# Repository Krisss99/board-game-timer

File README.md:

# board-game-timer
Timer measures players' time taken in their turn.

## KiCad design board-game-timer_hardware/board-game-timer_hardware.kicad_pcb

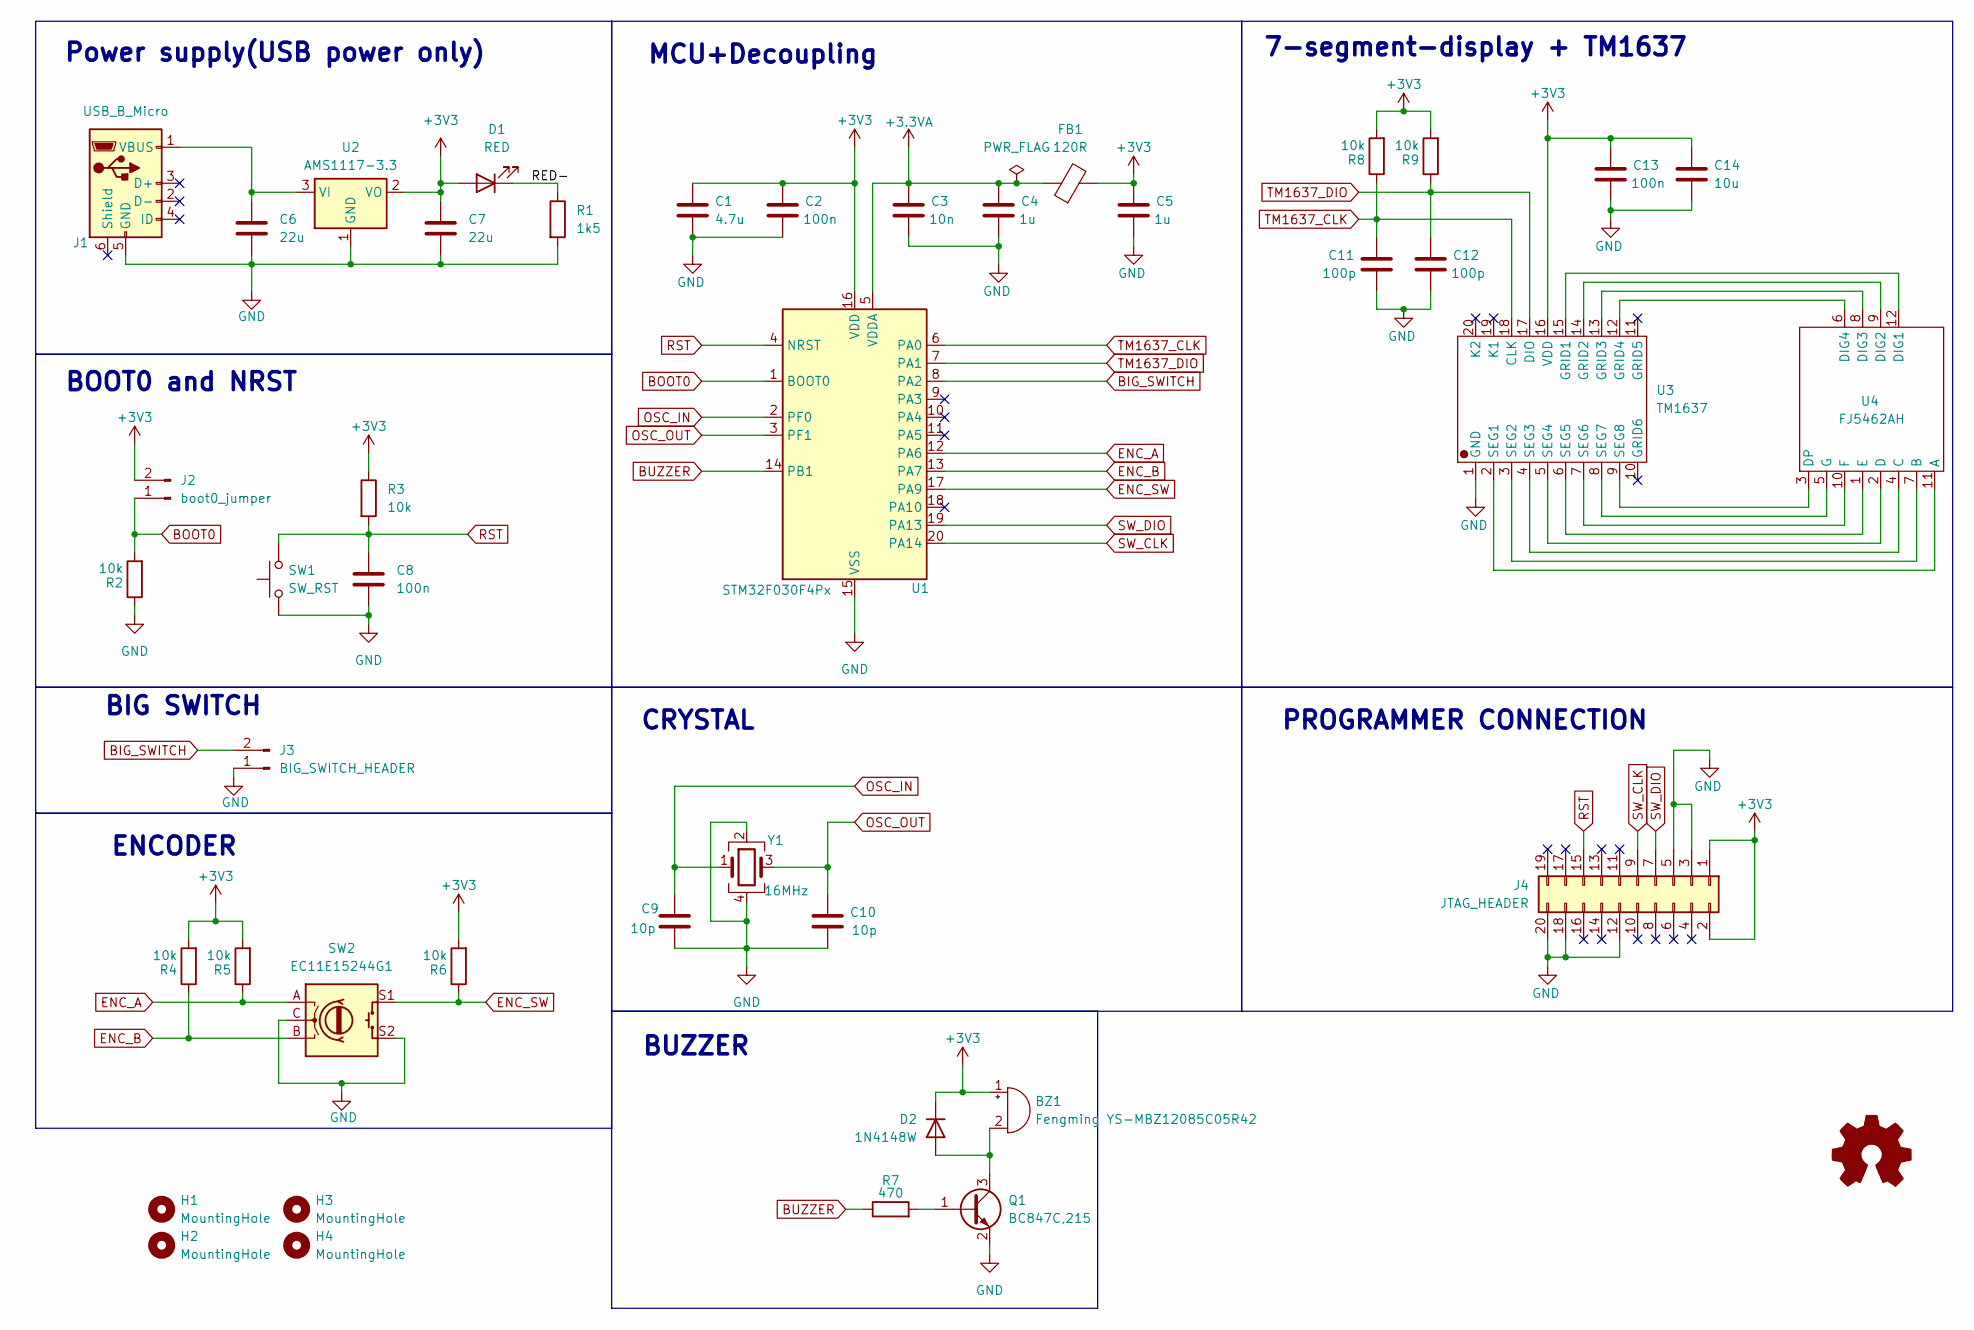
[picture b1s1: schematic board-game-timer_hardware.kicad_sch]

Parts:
BZ1: Fengming YS-MBZ12085C05R42; Buzzer_12x9.5RM7.6
C1: 4.7u; C_0805_2012Metric
C2, C8, C13: 100n; C_0402_1005Metric
C3: 10n; C_0402_1005Metric
C4, C5: 1u; C_0805_2012Metric
C6, C7: 22u; C_0805_2012Metric
C9, C10: 10p; C_0402_1005Metric
C11, C12: 100p; C_0402_1005Metric
C14: 10u; C_0805_2012Metric
D1: RED; LED_0603_1608Metric
D2: 1N4148W; D_SOD-123
FB1: 120R; L_0603_1608Metric
H1, H2, H3, H4: MountingHole; MountingHole_3.2mm_M3
J1: USB_B_Micro; USB_Micro-B_Amphenol_10118193-0001LF_Horizontal
J2: boot0_jumper; PinHeader_1x02_P2.54mm_Vertical
J3: BIG_SWITCH_HEADER; PinHeader_1x02_P2.54mm_Vertical
J4: JTAG_HEADER; PinHeader_2x10_P2.54mm_Vertical
Q1: BC847C,215; SOT-23-3
R1: 1k5; R_0402_1005Metric
R2, R3, R4, R5, R6, R8, R9: 10k; R_0402_1005Metric
R7: 470; R_0402_1005Metric
SW1: SW_RST; SW_PUSH_6mm
SW2: EC11E15244G1; RotaryEncoder_Alps_EC11E-Switch_Vertical_H20mm
U1: STM32F030F4Px; TSSOP-20_4.4x6.5mm_P0.65mm
U2: AMS1117-3.3; SOT-223-3_TabPin2
U3: TM1637
U4: FJ5462AH; ZHIHAO FJ5462AH
Y1: 16MHz; Crystal_SMD_3225-4Pin_3.2x2.5mm

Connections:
+3.3VA: C3.1, C4.1, FB1.1, U1.5 (VDDA)
+3V3: BZ1.1 (+), C1.1, C2.1, C5.1, C7.1, C13.1, C14.1, D1.2 (A), D2.1 (K), FB1.2, J2.2, J4.1, J4.2, R3.1, R4.2, R5.2, R6.2, R8.2, R9.2, U1.16 (VDD), U2.2 (VO), U3.16 (VDD)
/RED-: D1.1 (K), R1.1
BIG_SWITCH: J3.2, U1.8 (PA2)
BOOT0: J2.1, R2.2, U1.1 (BOOT0)
BUZZER: R7.1, U1.14 (PB1)
ENC_A: R5.1, SW2.A, U1.12 (PA6)
ENC_B: R4.1, SW2.B, U1.13 (PA7)
ENC_SW: R6.1, SW2.S1, U1.17 (PA9)
GND: C1.2, C2.2, C3.2, C4.2, C5.2, C6.2, C7.2, C8.2, C9.2, C10.2, C11.2, C12.2, C13.2, C14.2, J1.5 (GND), J3.1, J4.3, J4.5, J4.12, J4.18, J4.20, Q1.2 (E), R1.2, R2.1, SW1.1, SW2.C, SW2.S2, U1.15 (VSS), U2.1 (GND), U3.1 (GND), Y1.2, Y1.4
unnamed: BZ1.2 (-), D2.2 (A), Q1.3 (C)
unnamed: C6.1, J1.1 (VBUS), U2.3 (VI)
unnamed: Q1.1 (B), R7.2
unnamed: U3.15 (GRID1), U4.12 (DIG1)
unnamed: U3.14 (GRID2), U4.9 (DIG2)
unnamed: U3.13 (GRID3), U4.8 (DIG3)
unnamed: U3.12 (GRID4), U4.6 (DIG4)
unnamed: U3.2 (SEG1), U4.11 (A)
unnamed: U3.3 (SEG2), U4.7 (B)
unnamed: U3.4 (SEG3), U4.4 (C)
unnamed: U3.5 (SEG4), U4.2 (D)
unnamed: U3.6 (SEG5), U4.1 (E)
unnamed: U3.7 (SEG6), U4.10 (F)
unnamed: U3.8 (SEG7), U4.5 (G)
unnamed: U3.9 (SEG8), U4.3 (DP)
OSC_IN: C9.1, U1.2 (PF0), Y1.1
OSC_OUT: C10.1, U1.3 (PF1), Y1.3
RST: C8.1, J4.15, R3.2, SW1.2, U1.4 (NRST)
SW_CLK: J4.9, U1.20 (PA14)
SW_DIO: J4.7, U1.19 (PA13)
TM1637_CLK: C11.1, R8.1, U1.6 (PA0), U3.18 (CLK)
TM1637_DIO: C12.1, R9.1, U1.7 (PA1), U3.17 (DIO)

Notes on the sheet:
BIG SWITCH
PROGRAMMER CONNECTION
BOOT0 and NRST
ENCODER
BUZZER
Power supply(USB power only)
MCU+Decoupling
CRYSTAL
7-segment-display + TM1637

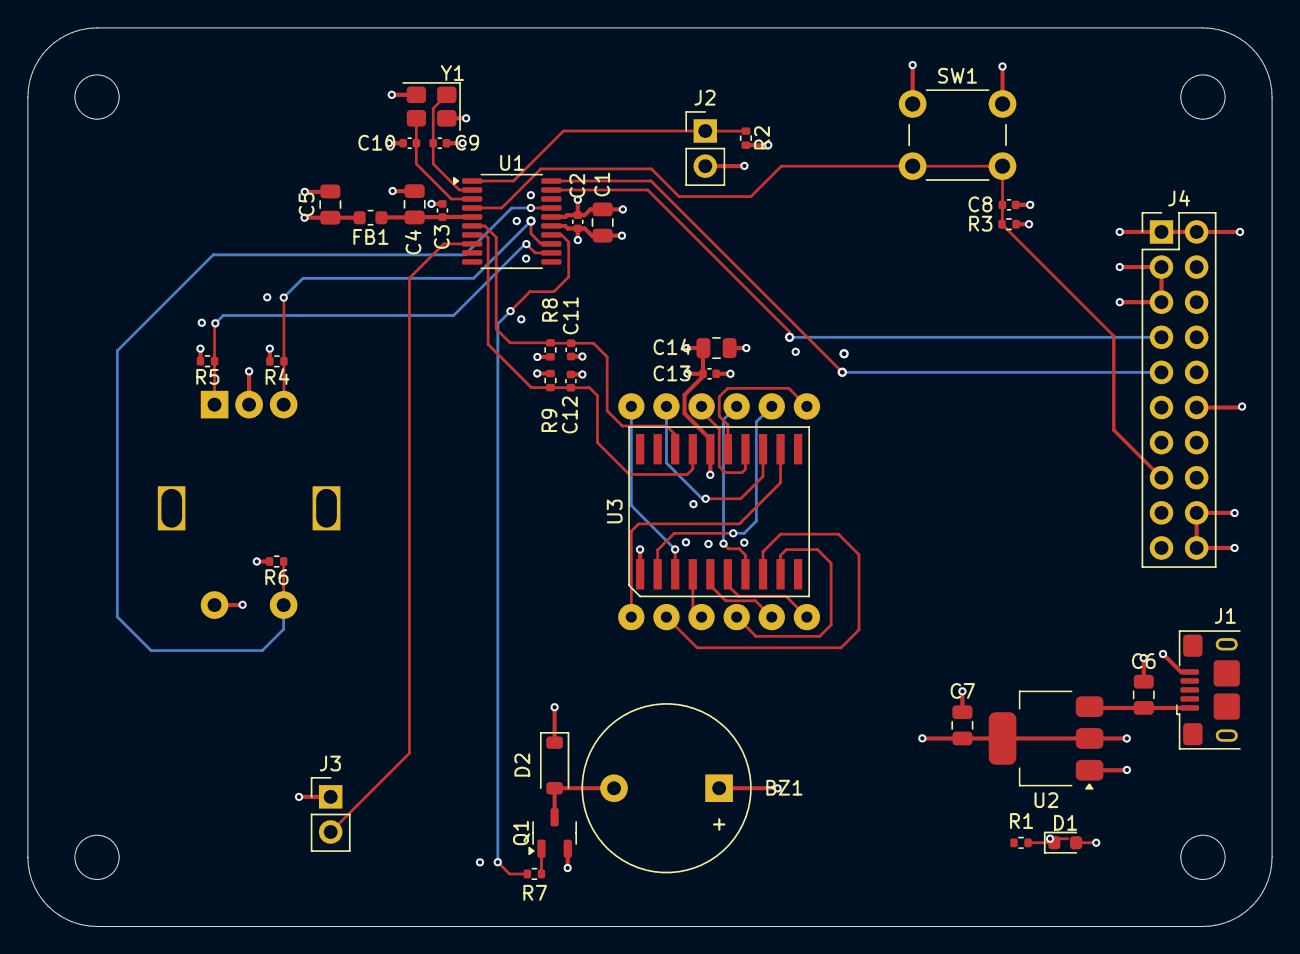
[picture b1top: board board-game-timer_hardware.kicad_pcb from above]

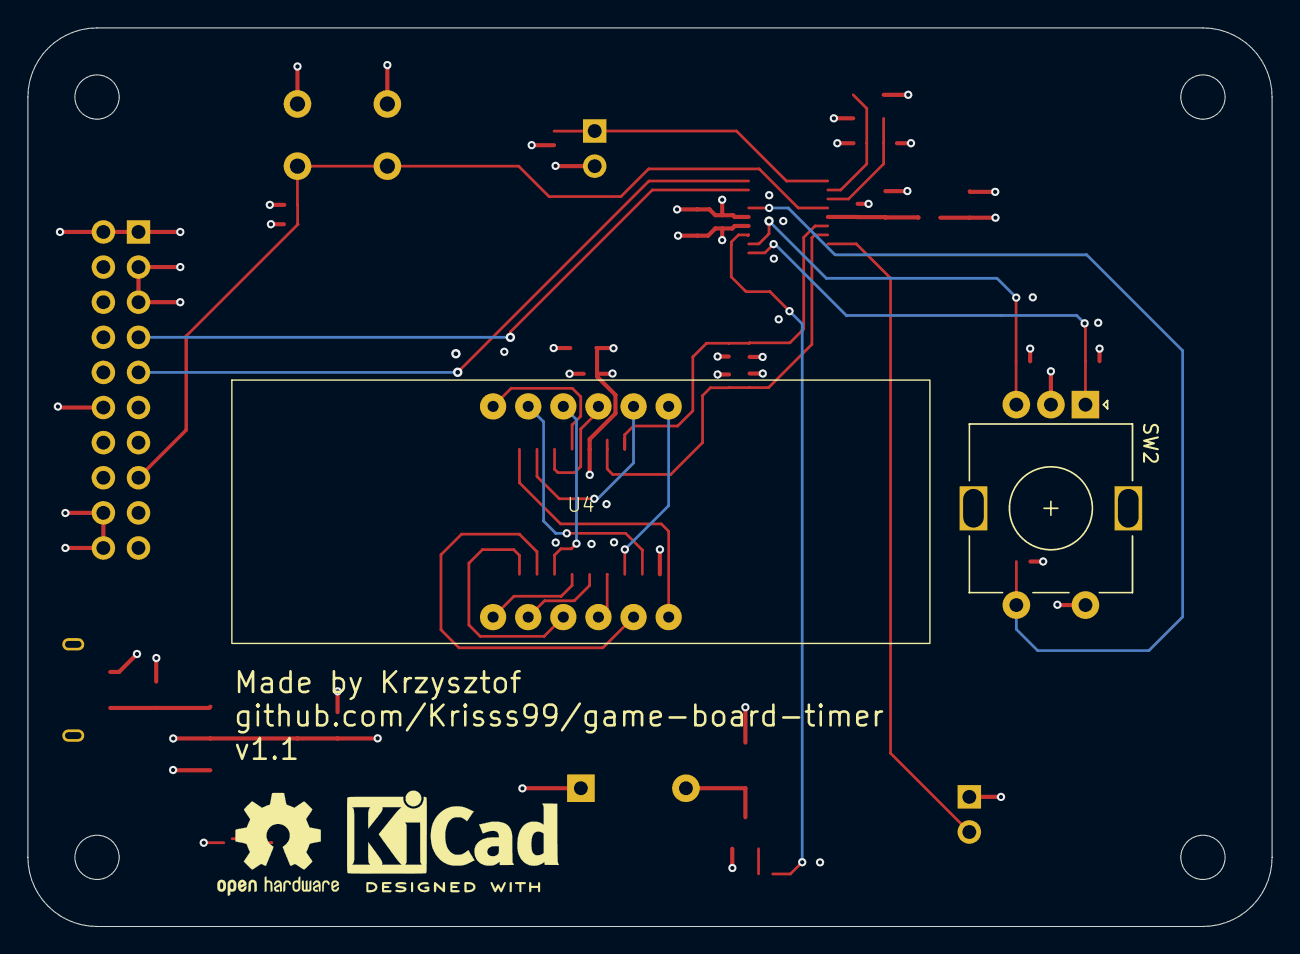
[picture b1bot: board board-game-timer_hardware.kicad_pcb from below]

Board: 4 copper layers, 90.0 x 65.0 mm, 43 parts (2 on the bottom side), 32 nets.

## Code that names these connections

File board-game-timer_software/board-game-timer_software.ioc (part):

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Mcu.Name=STM32F030F4Px
Mcu.Package=TSSOP20
Mcu.UserName=STM32F030F4Px
PA0.GPIOParameters=GPIO_Label
PA0.GPIO_Label=TM1637_CLK
PA0.Signal=GPIO_Output
PA1.GPIOParameters=GPIO_Label
PA1.GPIO_Label=TM1637_DIO
PA1.Signal=GPIO_Output
PA13.Mode=Serial_Wire
PA13.Signal=SYS_SWDIO
PA14.Mode=Serial_Wire
PA14.Signal=SYS_SWCLK
PA2.GPIOParameters=GPIO_PuPd,GPIO_Label
PA2.GPIO_Label=big_Button
PA2.GPIO_PuPd=GPIO_PULLUP
PA2.Signal=GPXTI2
PA6.Signal=S_TIM3_CH1
PA7.Signal=S_TIM3_CH2
PA9.GPIOParameters=GPIO_PuPd,GPIO_Label
PA9.GPIO_Label=ENCODER_Button
PA9.GPIO_PuPd=GPIO_PULLUP
PA9.Signal=GPXTI9
board=custom

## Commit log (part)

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2026-01-19 Adding LICENSE
2026-01-20 Updated gitignore
2026-01-20 Adding project files
2026-01-21 TM1637 working, but implementation not finished
    - TM1637 works as intented
    - Encoder and buttons are needed to work further
    with TM1637
2026-01-25 Encoder, encoderbutton and TM1637 intergrated.
    - Encoder button works with interrupt, starts/stops timer
    - Encoder can change time when timer not running
2026-01-26 All peripherals done, basic program works
    - Encoder and all buttons defined
    - TM1637 defined and working
    - Basic logic of the timer kinda works
    - Some issues persist when pressing big_button,
    encoder interrupt also triggers at the same moment
2026-01-26 All peripherals initialized and basic program works with some issues (#1)
    - Big button, encoder button and encoder work
    - TM1637 works and shows correct time (most of the time)
    - Basic program works
    - Some issues still present, see: [https://github.com/Krisss99/board-game-timer/issues](url)
2026-03-16 Added possibility to use colon
2026-03-16 Feature/tm1637
    - TM1637 working as intended
    - Possible with or without colon
2026-03-16 Final cleanups
    Everything works, but the encoder is not responsive as I would like to.
    - Removed unnecessery lines
    - Encoder works, but triggers double, time goes from 0 to 10 instead of
    0 to 5
    - Encoder will be fixed in next iteration
2026-03-16 Final cleanups
    Everything works, but the encoder is not responsive as I would like to.
    - Removed unnecessery lines
    - Encoder works, but triggers double, time goes from 0 to 10 instead of
    0 to 5
    - Encoder will be fixed in next iteration
    - Big button works
2026-03-16 Adding v0.1 of pcb. PCB ordered and in use. Next iteration will be fully developed without dev board.
2026-03-25 Adding blinking effect on screen
    - Effect added when choosing time with frequency of aprox 1 Hz
    - Simple testing shows it working
    - Rewritten main.c to make interrupt functions
    short as possible. Flags are checked in main loop
2026-03-25 Small changes to screen
    - Added control over colon between seconds and minutes
    - It is constantly on, but can be set on or off
    with the .colon_on
2026-03-25 Added features/Rewritten main.c (#7)
    This commit addresses two seperate problems:
    - Blinking effect
    - main logic and interrupts
    Blinking effect has been added and on when setting the time (or when powered on).
    In main.c:
    - Interrupt handlers are setting flags, so that interrupts can be cleared asap
2026-04-13 Adding schematic and PCB design for STM32F030F4P6
    - PCB designed around smaller and cheaper uC, to keep the cost low
    - All the features are the same compared to L432KC
    - The only loose modules are TM1637 screen and the encoder
2026-04-19 Rewritten and reconfigured for stm32f030f4
    - Configured peripherals to match PCB
    - Changed encoder from GPIO to TIM encoder mode
    - Removed encoder.c and .h, added code for TIM implementation
    - Changed delay in TM1637.h, as this implementation runs only 8MHz
    internal oscillator
    - "Blinking effect" on choosing time needs to be added again
2026-05-16 Small change
2026-05-16 F030f4p6 implementation (#8)
    Hardware changes:
    New schematic and PCB design around STM32F030F4P6 to keep cost low.
    Software changes:
    - Rewritten and reconfigured for stm32f030f4
    - All the features are the same compared to L432KC
    - Removed encoder.c and .h, added TIM implementation
2026-05-17 V1.1 work in progress
    - Added symbols for display and ic, rewired everything for one pcb
    - Added programmer header 2x10 for easier access
2026-05-25 PCB v1.1
    - Moved encoder, screen on the pcb
    - Added buzzer
    - Changed layer stackup to SIG/GND/PWR/SIG
